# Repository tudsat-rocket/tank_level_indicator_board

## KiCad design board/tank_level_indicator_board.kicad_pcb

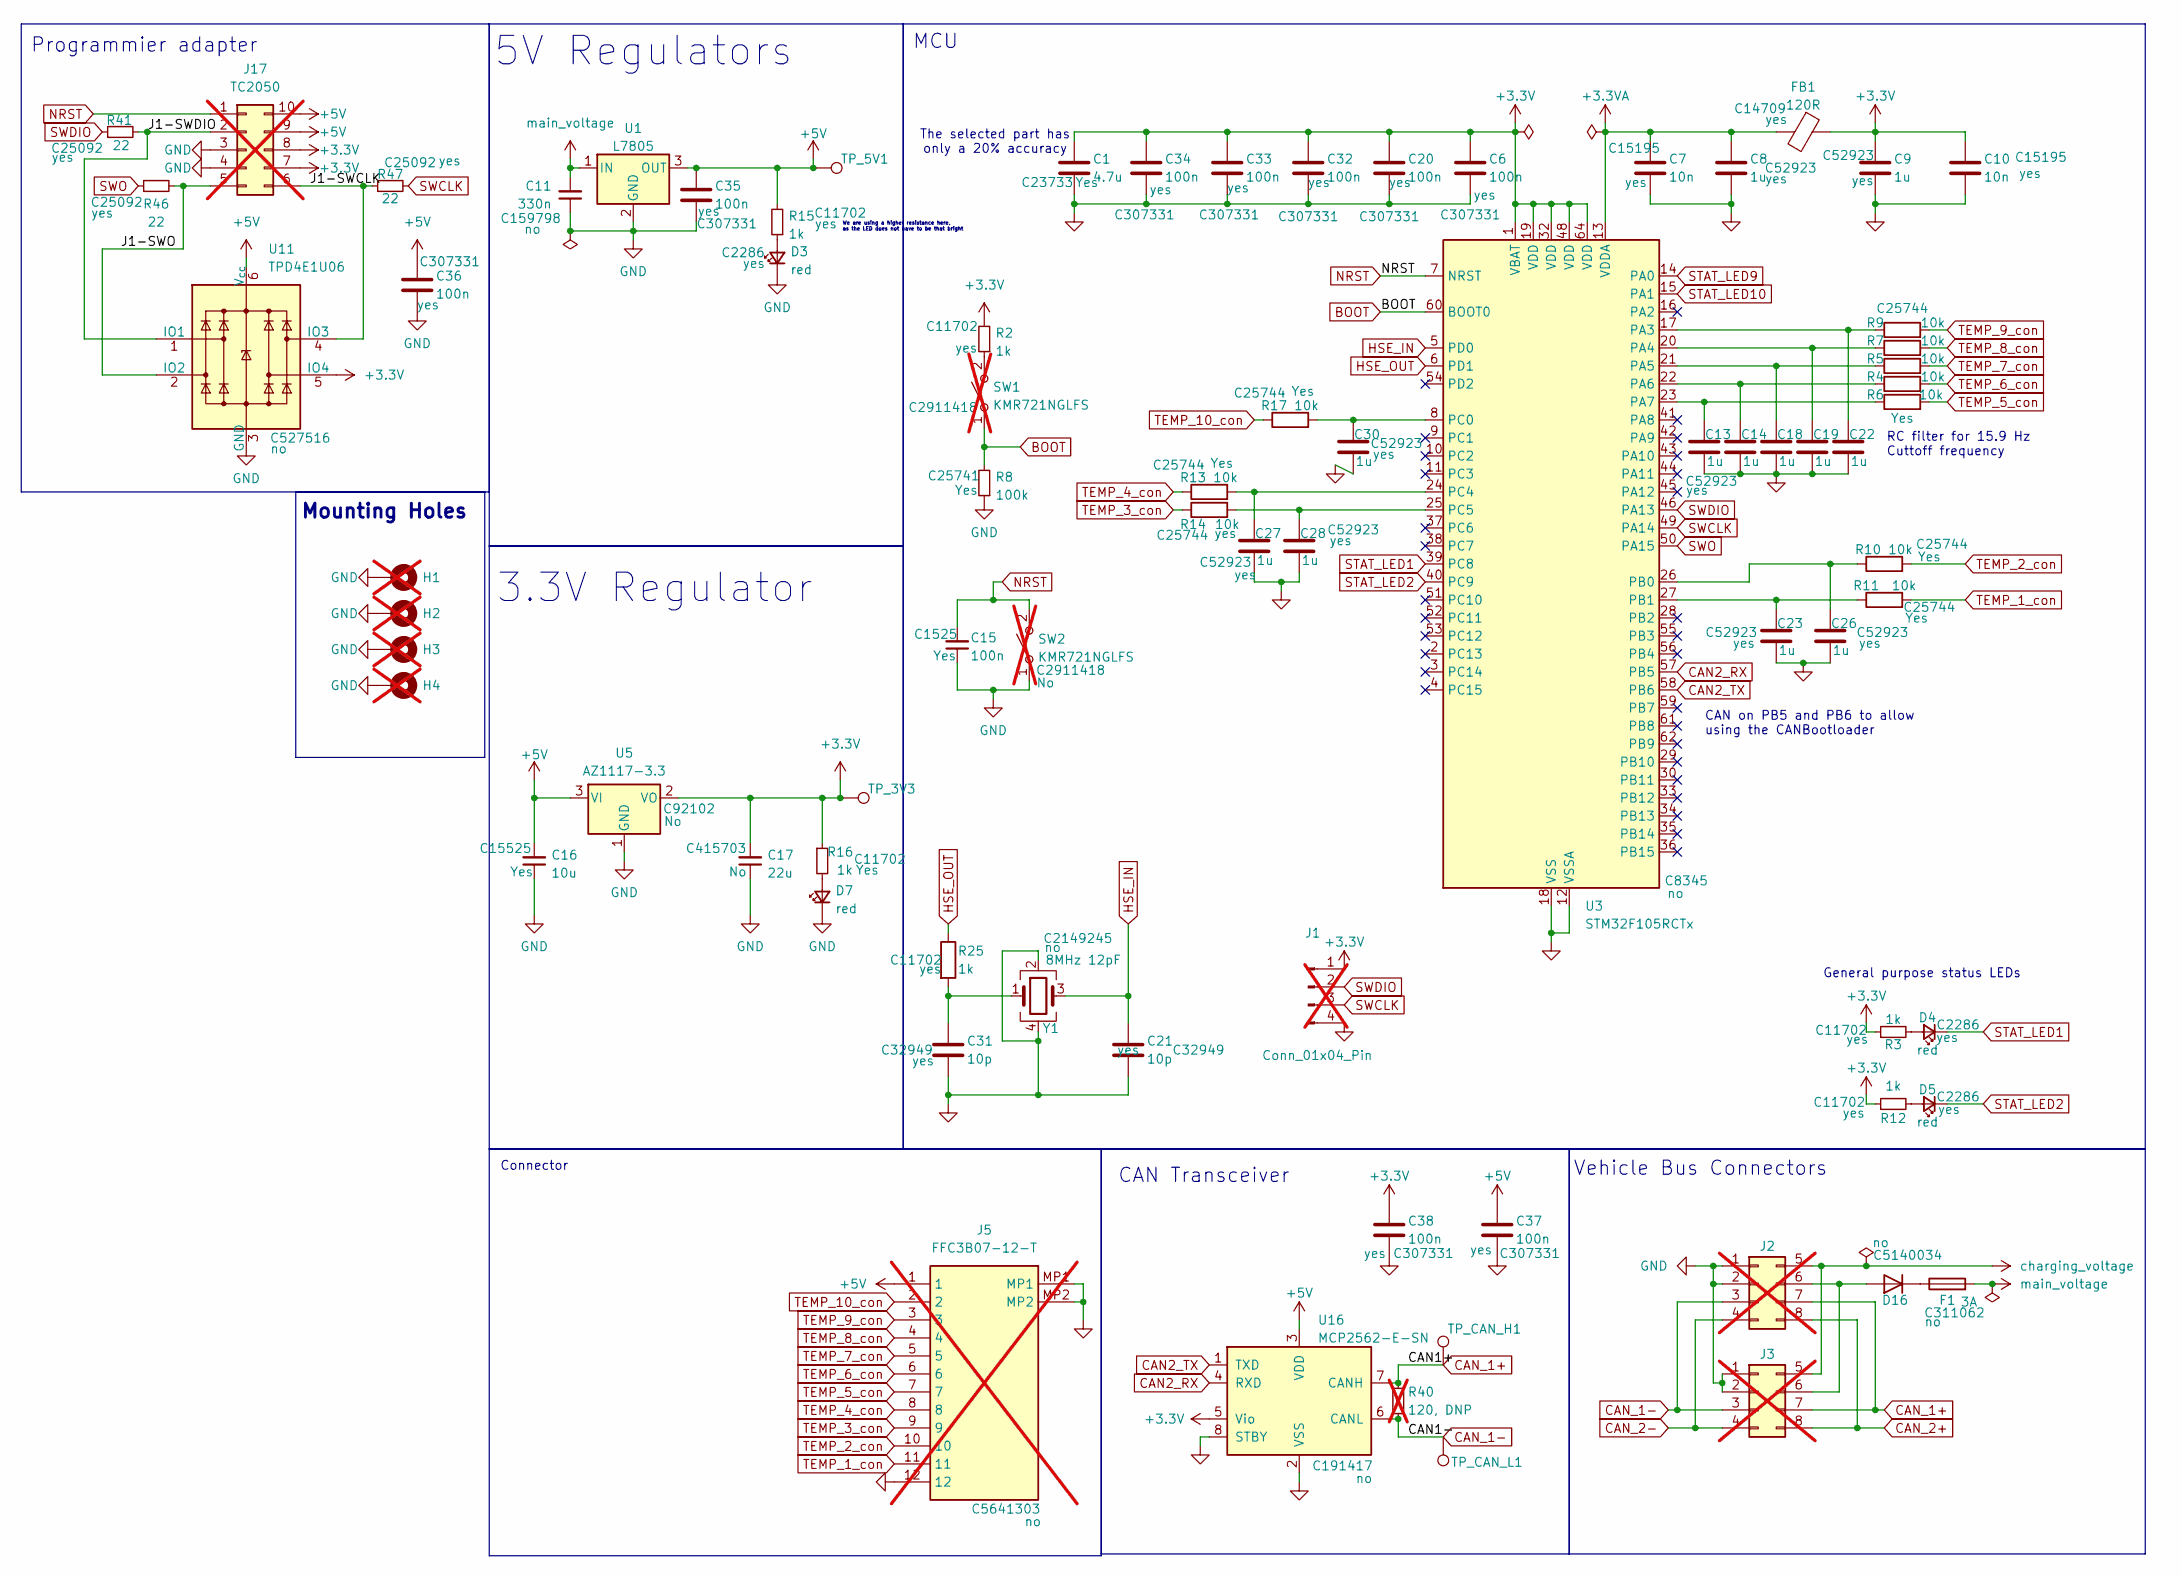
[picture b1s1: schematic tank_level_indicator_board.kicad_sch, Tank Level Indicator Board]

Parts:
C1: 4.7u; C_0402_1005Metric; LCSC C23733
C6, C20, C32, C33, C34, C35, C36, C37, C38: 100n; C_0402_1005Metric; LCSC C307331
C7, C10: 10n; C_0402_1005Metric; LCSC C15195
C8, C9, C13, C14, C18, C19, C22, C23, C26, C27, C28, C30: 1u; C_0402_1005Metric; LCSC C52923
C11: 330n; C_0603_1608Metric; Part# CL10B334KO8NNNC; LCSC C159798
C15: 100n; C_0402_1005Metric; Part# CL10B104KB8NNNC; LCSC C1525
C16: 10u; C_0402_1005Metric; LCSC C15525
C17: 22u; C_0402_1005Metric; Part# GRM155R60J226ME11D; LCSC C415703
C21, C31: 10p; C_0402_1005Metric; LCSC C32949
D3, D4, D5: red; LED_0603_1608Metric; LCSC C2286
D7: red; LED_0603_1608Metric; Part# 19-213/RSC-BS2T2B/3T; LCSC# C474026
D16: D; D_SMA; LCSC C5140034
F1: 3A; Fuse_0603_1608Metric_Pad1.05x0.95mm_HandSolder; LCSC C311062
FB1: 120R; L_0603_1608Metric; Part# BLM18PG121SN1D; LCSC C14709
H1, H2, H3, H4: MountingHole_Pad; MountingHole_3.2mm_M3_Pad_Via; Part# N/A; DigiKey# N/A; not fitted
J1: Conn_01x04_Pin; PinHeader_1x04_P1.27mm_Vertical_SMD_Pin1Left; not fitted
J2, J3: Conn_02x04_Top_Bottom; Molex_Micro-Fit_3.0_43045-0800_2x04_P3.00mm_Horizontal; not fitted
J5: FFC3B07-12-T; FFC3B0712T; Mouser Part Number 640-FFC3B07-12-T; not fitted
J17: TC2050; Tag-Connect_TC2050-IDC-FP_2x05_P1.27mm_Vertical; LCSC# x; not fitted
R2, R15: 1k; R_0402_1005Metric; Part# RC0603FR-0710KL; LCSC C11702
R3, R12, R16, R25: 1k; R_0402_1005Metric; LCSC C11702
R4, R5, R6, R7, R9, R10, R11, R13, R14, R17: 10k; R_0402_1005Metric; LCSC C25744
R8: 100k; R_0402_1005Metric; Part# RC0603FR-0710KL; LCSC C25741
R40: 120, DNP; R_0603_1608Metric_Pad0.98x0.95mm_HandSolder; LCSC x; not fitted
R41, R46, R47: 22; R_0402_1005Metric; Part# RC0603FR-0710KL; LCSC C25092
SW1, SW2: KMR721NGLFS; SW_Push_1P1T_NO_CK_KMR2; Part# KMR721NGLFS; LCSC C2911418; not fitted
TP_3V3: 3V3; TestPoint_Pad_D1.5mm
TP_5V1: 5V; TestPoint_Pad_D1.5mm
TP_CAN_H1: CAN_H; TestPoint_Pad_D1.5mm
TP_CAN_L1: CAN_L; TestPoint_Pad_D1.5mm
U1: L7805; TO-252-2; Part# L7805CDT-TR; LCSC# C310413
U3: STM32F105RCTx; LQFP-64_10x10mm_P0.5mm; LCSC C8345
U5: AZ1117-3.3; SOT-223-3_TabPin2; LCSC C92102
U11: TPD4E1U06; SOT-563; LCSC C527516
U16: MCP2562-E-SN; SOIC-8_3.9x4.9mm_P1.27mm; Part# MCP2562T-E/SN; LCSC C191417
Y1: 8MHz 12pF; Crystal_SMD_5032-4Pin_5.0x3.2mm; Part# 5TJ480000NYLBC; LCSC C2149245

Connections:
+3.3V: C1.1, C6.1, C9.1, C10.1, C17.2, C20.1, C32.1, C33.1, C34.1, C38.1, FB1.1, J1.1, J17.7, J17.8, R2.2, R3.1, R12.1, R16.1, TP_3V3.1 (1_1), U3.1 (VBAT), U3.19 (VDD), U3.32 (VDD), U3.48 (VDD), U3.64 (VDD), U5.2 (VO), U11.5 (IO4), U16.5 (Vio)
+3.3VA: C7.1, C8.1, FB1.2, U3.13 (VDDA)
+5V: C16.2, C35.1, C36.1, C37.1, J5.1, J17.9, J17.10, R15.2, TP_5V1.1 (1_1), U1.3 (OUT), U5.3 (VI), U11.6 (V_{cc}), U16.3 (VDD)
/J1-SWCLK: J17.6, R47.1, U11.4 (IO3)
/J1-SWDIO: J17.2, R41.2, U11.1 (IO1)
/J1-SWO: J17.5, R46.2, U11.2 (IO2)
BOOT: R8.2, SW1.1 (A), U3.60 (BOOT0)
CAN2_RX: U3.57 (PB5), U16.4 (RXD)
CAN2_TX: U3.58 (PB6), U16.1 (TXD)
CAN_1+: J2.7, J3.7, R40.1, TP_CAN_H1.1 (1_1), U16.7 (CANH)
CAN_1-: J2.3, J3.3, R40.2, TP_CAN_L1.1 (1_1), U16.6 (CANL)
CAN_2+: J2.8, J3.8
CAN_2-: J2.4, J3.4
GND: C1.2, C6.2, C7.2, C8.2, C9.2, C10.2, C11.1, C13.2, C14.2, C15.1, C16.1, C17.1, C18.2, C19.2, C20.2, C21.2, C22.2, C23.2, C26.2, C27.2, C28.2, C30.2, C31.2, C32.2, C33.2, C34.2, C35.2, C36.2, C37.2, C38.2, D3.1 (K), D7.1 (K), H1.1 (1_1), H2.1 (1_1), H3.1 (1_1), H4.1 (1_1), J1.4, J2.1, J2.2, J3.1, J3.2, J5.12, J5.MP1, J5.MP2, J17.3, J17.4, R8.1, SW2.1 (A), U1.2 (GND), U3.12 (VSSA), U3.18 (VSS), U3.31 (VSS), U3.47 (VSS), U3.63 (VSS), U5.1 (GND), U11.3 (GND), U16.2 (VSS), U16.8 (STBY), Y1.2, Y1.4
HSE_IN: C21.1, U3.5 (PD0), Y1.3
HSE_OUT: R25.1, U3.6 (PD1)
NRST: C15.2, J17.1, SW2.2 (B), U3.7 (NRST)
unnamed: C31.1, R25.2, Y1.1
unnamed: D3.2 (A), R15.1
unnamed: D4.2 (A), R3.2
unnamed: D5.2 (A), R12.2
unnamed: D7.2 (A), R16.2
unnamed: D16.2 (A), J2.6, J3.6
unnamed: D16.1 (K), F1.1
unnamed: R2.1, SW1.2 (B)
unnamed: C22.1, R9.1, U3.17 (PA3)
unnamed: C19.1, R7.1, U3.20 (PA4)
unnamed: C18.1, R5.1, U3.21 (PA5)
unnamed: C14.1, R4.1, U3.22 (PA6)
unnamed: C13.1, R6.1, U3.23 (PA7)
unnamed: C26.1, R10.1, U3.26 (PB0)
unnamed: C23.1, R11.1, U3.27 (PB1)
unnamed: C30.1, R17.2, U3.8 (PC0)
unnamed: C27.1, R13.2, U3.24 (PC4)
unnamed: C28.1, R14.2, U3.25 (PC5)
STAT_LED1: D4.1 (K), U3.39 (PC8)
STAT_LED2: D5.1 (K), U3.40 (PC9)
STAT_LED9: U3.14 (PA0)
STAT_LED10: U3.15 (PA1)
SWCLK: J1.3, R47.2, U3.49 (PA14)
SWDIO: J1.2, R41.1, U3.46 (PA13)
SWO: R46.1, U3.50 (PA15)
TEMP_1_con: J5.11, R11.2
TEMP_2_con: J5.10, R10.2
TEMP_3_con: J5.9, R14.1
TEMP_4_con: J5.8, R13.1
TEMP_5_con: J5.7, R6.2
TEMP_6_con: J5.6, R4.2
TEMP_7_con: J5.5, R5.2
TEMP_8_con: J5.4, R7.2
TEMP_9_con: J5.3, R9.2
TEMP_10_con: J5.2, R17.1
charging_voltage: J2.5, J3.5
main_voltage: C11.2, F1.2, U1.1 (IN)

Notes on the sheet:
We are using a higher resistance here, as the LED does not have to be that bright
Connector
CAN Transceiver
Mounting Holes
5V Regulators
MCU
RC filter for 15.9 Hz Cuttoff frequency
3.3V Regulator
Programmier adapter
CAN on PB5 and PB6 to allow using the CANBootloader
The selected part has only a 20% accuracy
General purpose status LEDs
Vehicle Bus Connectors

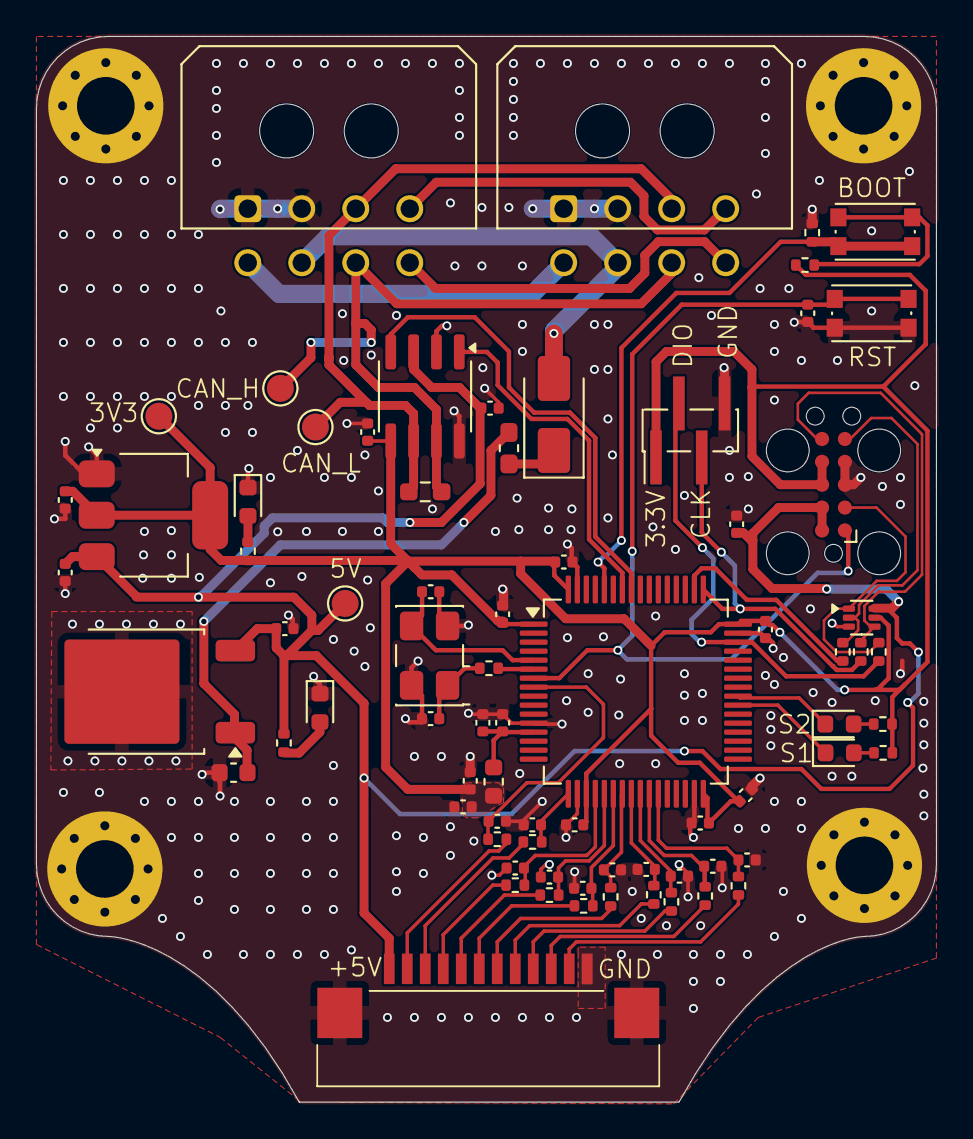
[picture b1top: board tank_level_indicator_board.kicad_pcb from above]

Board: 2 copper layers, 50.0 x 59.2 mm, 79 parts (0 on the bottom side), 52 nets.

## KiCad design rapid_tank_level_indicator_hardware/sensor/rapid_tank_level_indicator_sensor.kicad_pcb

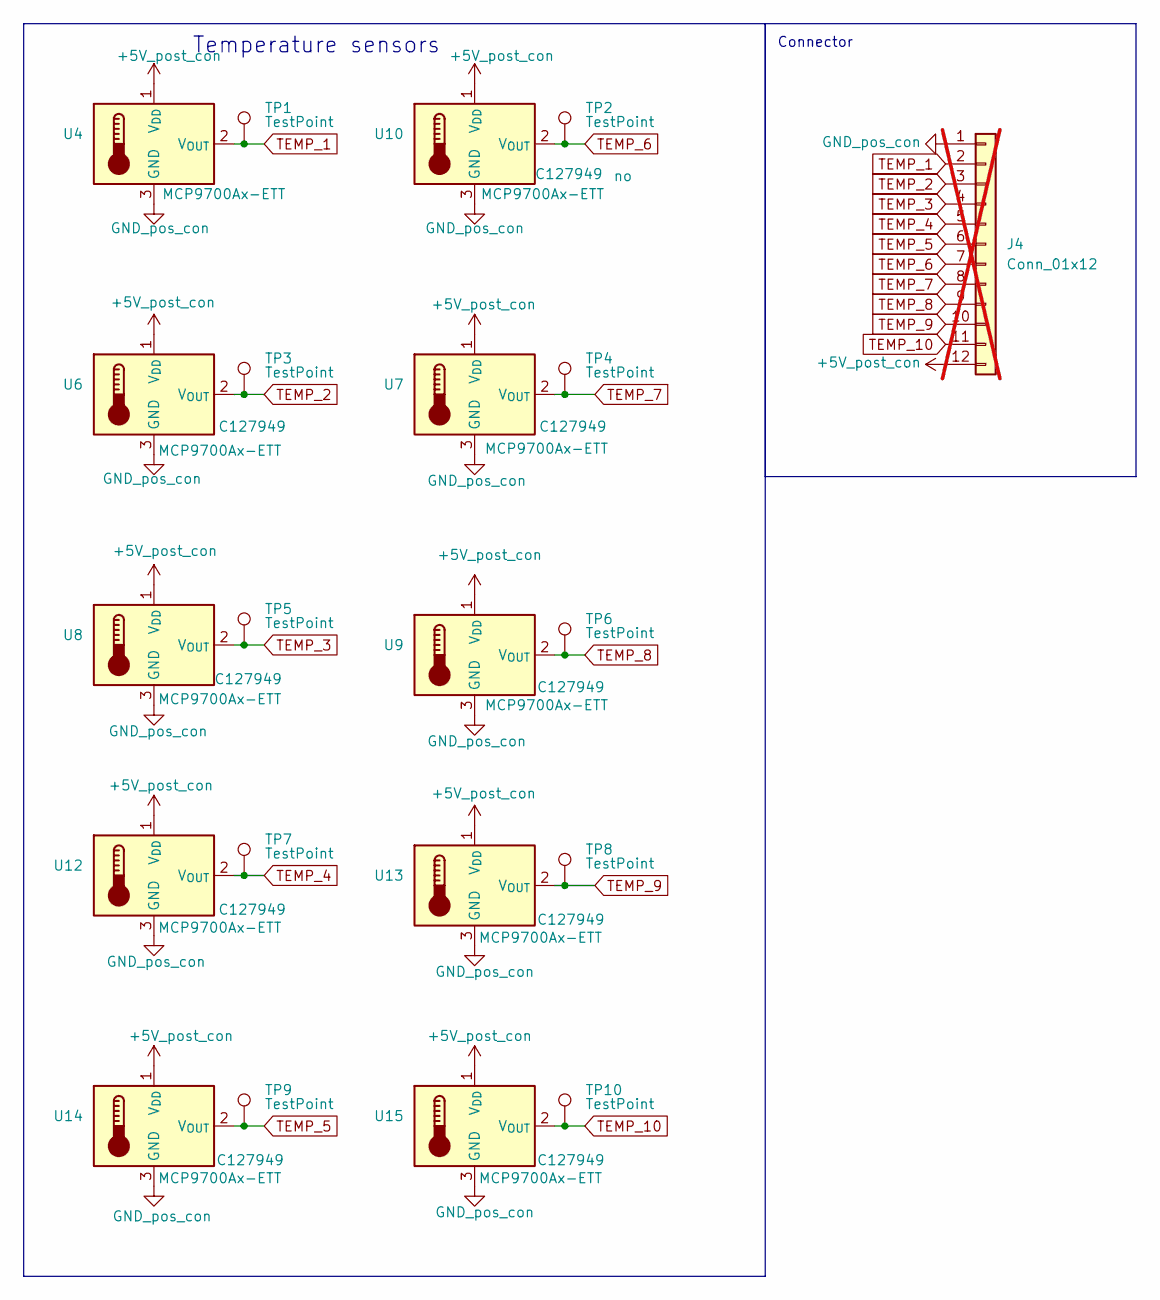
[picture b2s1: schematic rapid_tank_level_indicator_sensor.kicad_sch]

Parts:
J4: Conn_01x12; FFC3B07_pad; not fitted
TP1, TP2, TP3, TP4, TP5, TP6, TP7, TP8, TP9, TP10: TestPoint; TestPoint_Pad_D1.0mm
U4, U6, U7, U8, U9, U10, U12, U13, U14, U15: MCP9700Ax-ETT; SOT-23; LCSC C127949

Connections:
+5V_post_con: J4.12, U4.1 (V_{DD}), U6.1 (V_{DD}), U7.1 (V_{DD}), U8.1 (V_{DD}), U9.1 (V_{DD}), U10.1 (V_{DD}), U12.1 (V_{DD}), U13.1 (V_{DD}), U14.1 (V_{DD}), U15.1 (V_{DD})
GND_pos_con: J4.1, U4.3 (GND), U6.3 (GND), U7.3 (GND), U8.3 (GND), U9.3 (GND), U10.3 (GND), U12.3 (GND), U13.3 (GND), U14.3 (GND), U15.3 (GND)
TEMP_1: J4.2, TP1.1 (1_1), U4.2 (V_{OUT})
TEMP_2: J4.3, TP3.1 (1_1), U6.2 (V_{OUT})
TEMP_3: J4.4, TP5.1 (1_1), U8.2 (V_{OUT})
TEMP_4: J4.5, TP7.1 (1_1), U12.2 (V_{OUT})
TEMP_5: J4.6, TP9.1 (1_1), U14.2 (V_{OUT})
TEMP_6: J4.7, TP2.1 (1_1), U10.2 (V_{OUT})
TEMP_7: J4.8, TP4.1 (1_1), U7.2 (V_{OUT})
TEMP_8: J4.9, TP6.1 (1_1), U9.2 (V_{OUT})
TEMP_9: J4.10, TP8.1 (1_1), U13.2 (V_{OUT})
TEMP_10: J4.11, TP10.1 (1_1), U15.2 (V_{OUT})

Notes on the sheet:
Connector
Temperature sensors

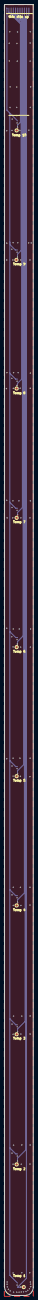
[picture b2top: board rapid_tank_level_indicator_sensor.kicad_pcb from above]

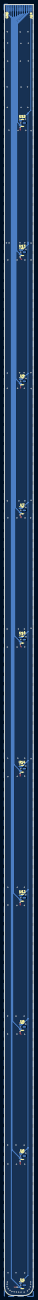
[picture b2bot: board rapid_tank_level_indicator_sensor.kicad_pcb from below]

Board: 2 copper layers, 13.0 x 583.2 mm, 21 parts (11 on the bottom side), 12 nets.

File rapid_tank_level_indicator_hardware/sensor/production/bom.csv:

Designator,Footprint,Quantity,Value,LCSC Part #
"TP1, TP10, TP2, TP3, TP4, TP5, TP6, TP7, TP8, TP9",TestPoint_Pad_D1.0mm,10,TestPoint,
"U10, U12, U13, U14, U15, U4, U6, U7, U8, U9",SOT-23,10,MCP9700Ax-ETT,C127949

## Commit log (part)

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2025-09-29 init
2025-11-04 finish design
2026-05-10 check LCSC parts and small layout adjustments
2026-06-03 split board in two projects
2026-06-14 last edits
